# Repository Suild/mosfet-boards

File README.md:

# mosfet-boards
Schematics and board files for MOSFET boards

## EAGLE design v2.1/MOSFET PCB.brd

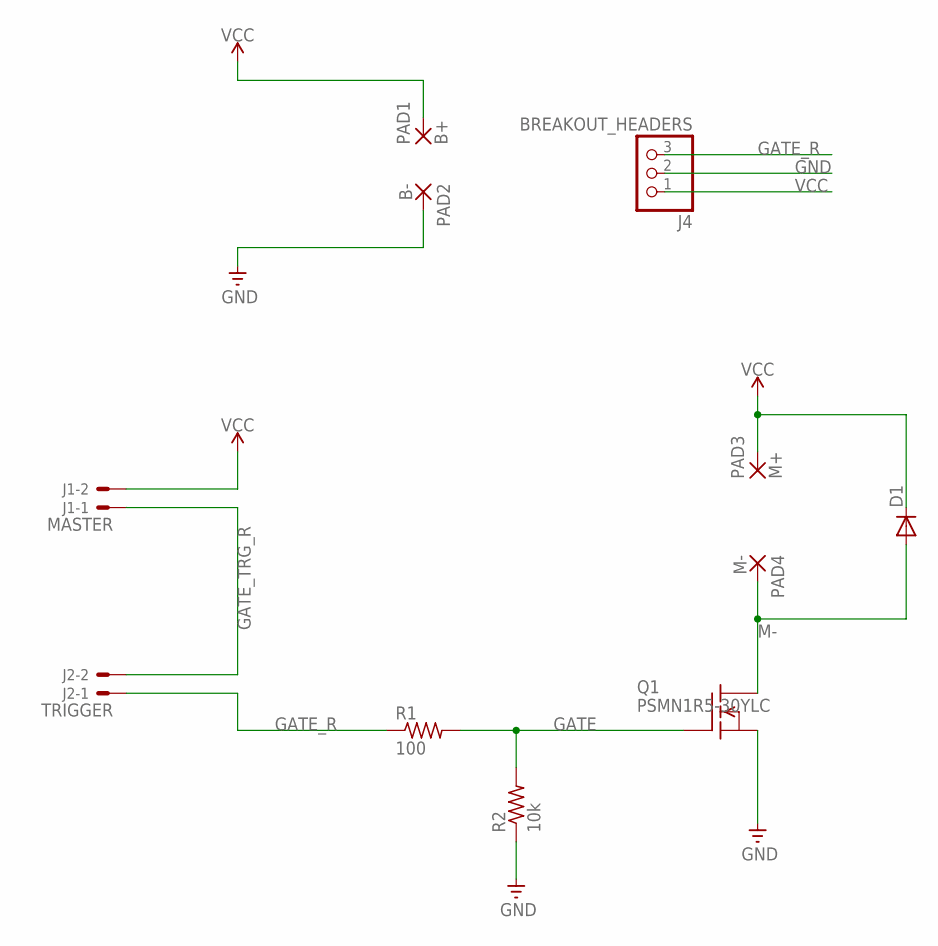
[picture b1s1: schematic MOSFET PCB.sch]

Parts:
D1: S2A; DO214AA
J1: MASTER; JST-XH-02-PACKAGE-ROUND-PAD
J2: TRIGGER; JST-XH-02-PACKAGE-ROUND-PAD
J4: BREAKOUT_HEADERS; 1X03
PAD1: B+; 5-2,5
PAD2: B-; 5-2,5
PAD3: M+; 5-2,5
PAD4: M-; 5-2,5
Q1: PSMN1R5-30YLC; TO127P600X120-5N
R1: 100; M0805
R2: 10k; M0805

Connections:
GATE: Q1.4 (G), R1.2, R2.2
GATE_R: J2.1, J4.3, R1.1
GATE_TRG_R: J1.1, J2.2
GND: J4.2, PAD2.1, Q1.1 (S), Q1.2 (S), Q1.3 (S), R2.1
M-: D1.A, PAD4.1, Q1.5 (D)
VCC: D1.C, J1.2, J4.1, PAD1.1, PAD3.1

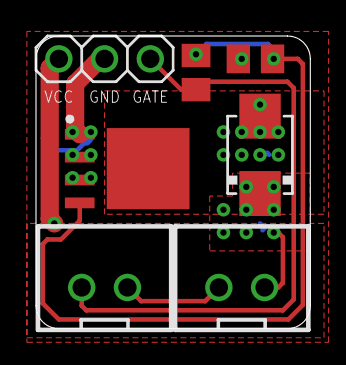
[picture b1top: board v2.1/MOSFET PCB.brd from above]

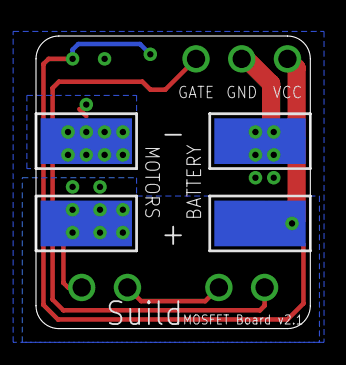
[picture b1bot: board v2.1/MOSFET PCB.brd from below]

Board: 2 copper layers, 15.2 x 16.3 mm, 11 parts (4 on the bottom side), 6 nets.

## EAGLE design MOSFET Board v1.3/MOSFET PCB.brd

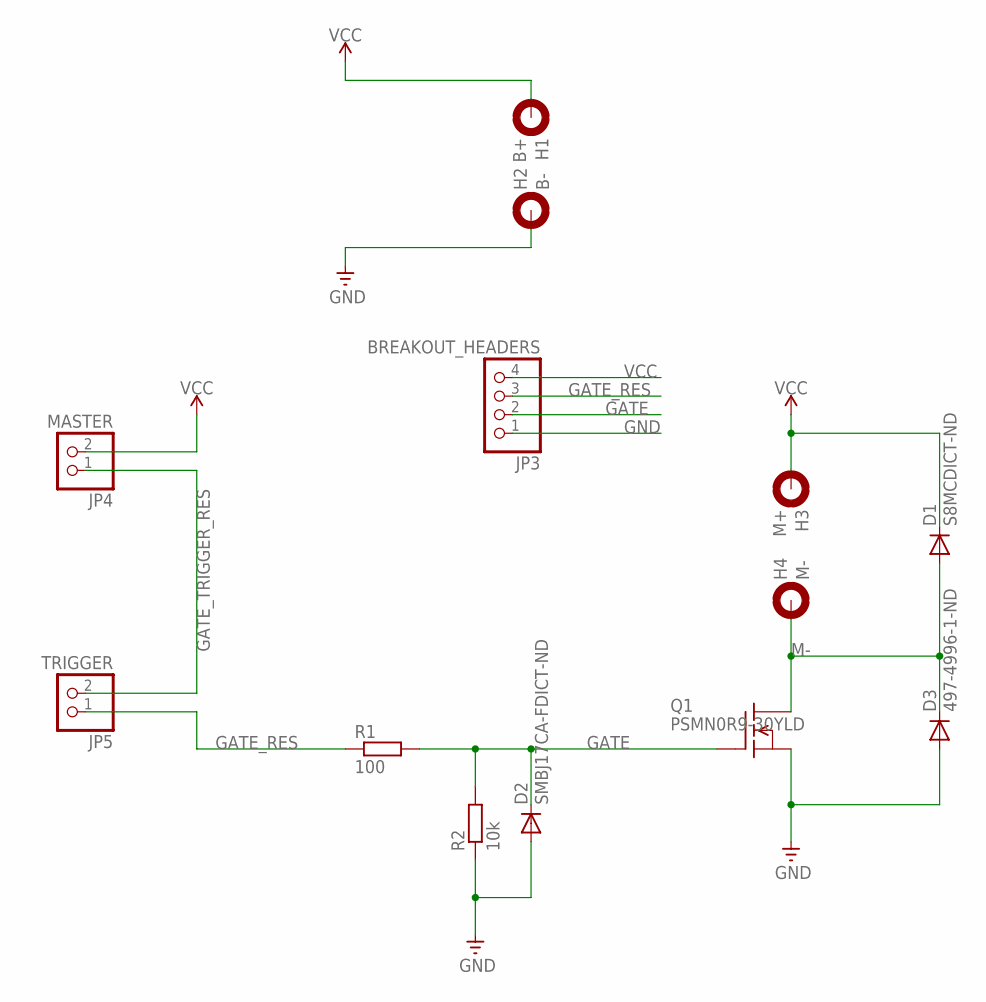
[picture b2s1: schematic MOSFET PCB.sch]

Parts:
D1: S8MCDICT-ND; DO214AB
D2: SMBJ17CA-FDICT-ND; DO214AA
D3: 497-4996-1-ND; DO214AB
H1: B+; MOUNT-HOLE-2.5MM
H2: B-; MOUNT-HOLE-2.5MM
H3: M+; MOUNT-HOLE-2.5MM
H4: M-; MOUNT-HOLE-2.5MM
JP3: BREAKOUT_HEADERS; 1X04
JP4: MASTER; 1X02
JP5: TRIGGER; 1X02
Q1: PSMN0R9-30YLD; LFPAK-EXTENDED-LEGS
R1: 100; R1206
R2: 10k; R1206

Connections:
GATE: D2.C, JP3.2, Q1.4 (G), R1.2, R2.2
GATE_RES: JP3.3, JP5.1, R1.1
GATE_TRIGGER_RES: JP4.1, JP5.2
GND: D2.A, D3.A, H2.P$1, JP3.1, Q1.1 (S), Q1.2 (S), Q1.3 (S), R2.1
M-: D1.A, D3.C, H4.P$1, Q1.5 (D)
VCC: D1.C, H1.P$1, H3.P$1, JP3.4, JP4.2

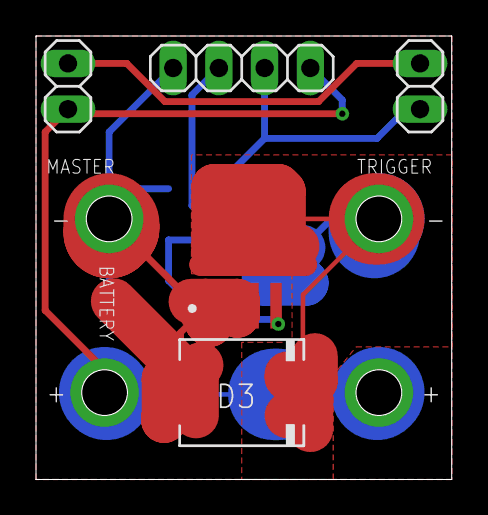
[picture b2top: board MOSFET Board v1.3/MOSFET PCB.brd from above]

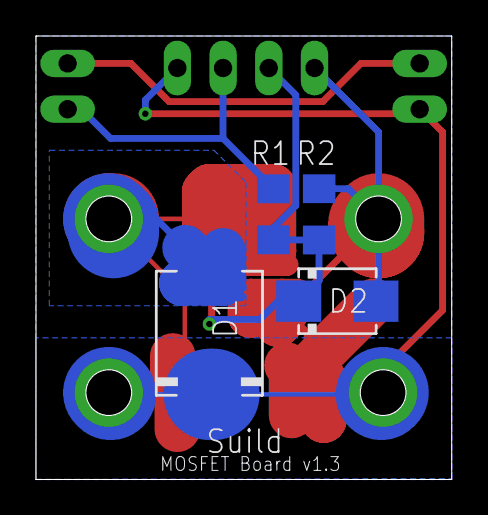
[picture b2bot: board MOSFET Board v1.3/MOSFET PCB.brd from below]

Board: 2 copper layers, 23.1 x 24.6 mm, 13 parts (4 on the bottom side), 6 nets.

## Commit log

2019-03-27 Add files for MOSFET board v1.3
2019-10-27 add files for v2.1'

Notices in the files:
parts and their libraries:
SparkFun-Aesthetics: Licensing: Creative Commons ShareAlike 4.0 International - https://creativecommons.org/licenses/by-sa/4.0
